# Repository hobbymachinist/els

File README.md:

# STM32 - Electronic Leadscrew

Electronic Leadscrew with STM32

## Demos

Some short demos available on YouTube

https://www.youtube.com/channel/UCVE05OvPm0yVd1yQSVZ0YSA/videos

## Building

```
git clone https://github.com/libopencm3/libopencm3
export OPENCM3_DIR=$PWD/libopencm3

cd libopencm3
make

cd ../
git clone <repo-url>
cd els

# edit Makefile to pick target and a TFT version
make TFT=ILI9481

# or
make TFT=ILI9486

# or
make TFT=ILI9488
```

Some ILITEK ICs use a non-standard 556 16-bit colorspace, use `COLORS=TFT_RGB_556` option in that case.

```
make TFT=ILI9488 COLORS=TFT_RGB_556
```

## Technical documentation

See [Technical Documentation](docs/els.md)

## Design ideas & Reference

- https://github.com/clough42/electronic-leadscrew
- https://github.com/prototypicall/Didge

## Goals / Features

1. The initial software is going to focus on being functional.
2. There is huge scope for optimisation, which can be something I might look into down the track.
3. Eventually, I'd like to add a G-code parser and motion controller to enable optional CNC control.

### Working with limited testing

* Z axis control for manual turning and threading operations
* Soft limits on Z & X
* Hard limits on Z & X
* Backlash compensation for leadscrews
* Semi automated cycles:
    - Turning
    - Threading
    - External Tapers
    - Internal Tapers
    - External Arcs
* Optional DRO support for:
    - TTL optical scales

### Wishlist / TO DO

* Semi automated cycles:
    - Internal Arc
    - External groove
    - Internal groove
* Tool radius compensation

## Pull Requests

Please reach out to discuss any major rewrites or changes if you wish to merge the changes upstream.

A lot of the firmware was developed over a few years on and off when I could find time to code and think about how I'd use it.
I don't want to disappoint or stop anyone from improving the software or hardware design but the primary focus of this work is
for my own personal use and don't want anything to distract me from that in a significant fashion. I don't have plenty of spare
time to review design changes or major software changes.

## IMPORTANT - PLEASE READ

Lathes are not toys, you can get injured or hurt someone else if you're not careful. Use this software at your
own risk.

This software is not provided with any warranty or support. It has only had limited testing in a home / hobby use setting
and may result in you getting injured or your equipment getting damaged due to errors in programming.

The author does not take any responsibility for the use of this software by others and cannot be held liable for any damages
that may result from its use.

## LICENSE

https://opensource.org/licenses/GPL-3.0

Free to be used in any fashion without royalty but any changes to hardware or software should be attributed and publicly shared
for the benefit of others.

Some of the code in this project uses snippets of code from [Adafruit GFX](https://github.com/adafruit/Adafruit-GFX-Library/)

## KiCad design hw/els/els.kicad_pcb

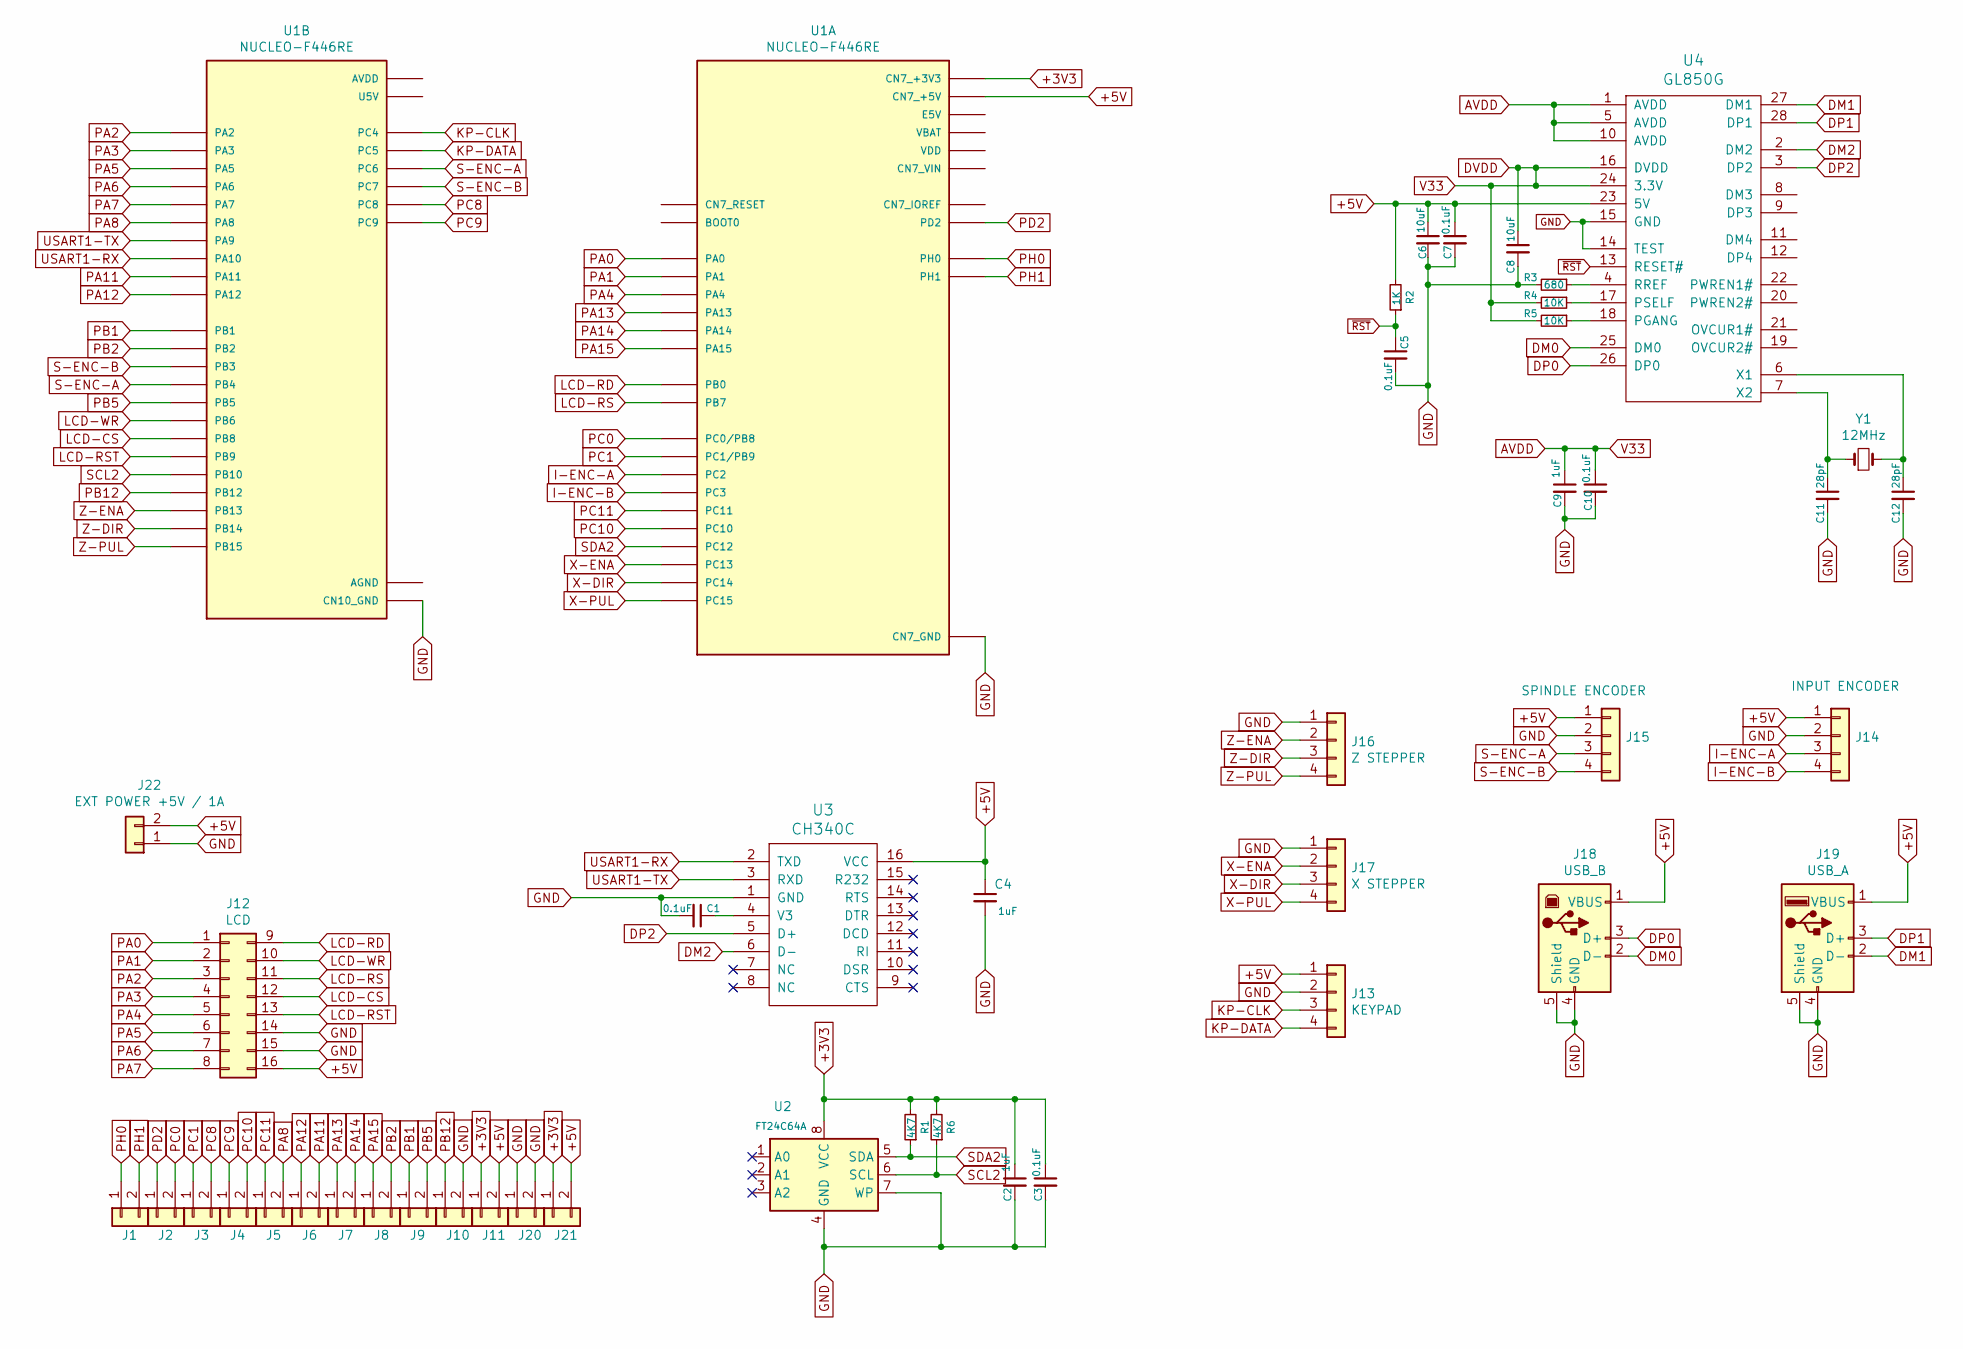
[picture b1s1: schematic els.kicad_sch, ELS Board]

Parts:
C1, C3, C5, C7, C10: 0.1uF; C_0805_2012Metric_Pad1.15x1.40mm_HandSolder
C2, C4, C9: 1uF; C_0805_2012Metric_Pad1.15x1.40mm_HandSolder
C6, C8: 10uF; C_0805_2012Metric_Pad1.15x1.40mm_HandSolder
C11, C12: 28pF; C_0805_2012Metric_Pad1.15x1.40mm_HandSolder
J1, J2, J3, J4, J5, J6, J7, J8, J9, J10, J11, J20, J21: Conn_01x02; TerminalBlock_bornier-2_P5.08mm
J12: LCD; IDC-Header_2x08_P2.54mm_Vertical
J13: KEYPAD; PinSocket_1x04_P2.54mm_Vertical
J14: INPUT ENCODER; PinSocket_1x04_P2.54mm_Vertical
J15: SPINDLE ENCODER; PinSocket_1x04_P2.54mm_Vertical
J16: Z STEPPER; PinSocket_1x04_P2.54mm_Vertical
J17: X STEPPER; PinSocket_1x04_P2.54mm_Vertical
J18: USB_B; USB_B_OST_USB-B1HSxx_Horizontal
J19: USB_A; USB_A_CONNFLY_DS1095-WNR0
J22: EXT POWER +5V / 1A; TerminalBlock_bornier-2_P5.08mm
R1, R6: 4K7; R_0805_2012Metric_Pad1.15x1.40mm_HandSolder
R2: 1K; R_0805_2012Metric_Pad1.15x1.40mm_HandSolder
R3: 680; R_0805_2012Metric_Pad1.15x1.40mm_HandSolder
R4, R5: 10K; R_0805_2012Metric_Pad1.15x1.40mm_HandSolder
U1: NUCLEO-F446RE; MODULE_NUCLEO-F446RE; PARTREV 13
U2: FT24C64A; SO-8_5.3x6.2mm_P1.27mm
U3: CH340C; SOIC-16_3.9x9.9mm_P1.27mm
U4: GL850G; SSOP-28_5.3x10.2mm_P0.65mm
Y1: 12MHz; Crystal_HC49-4H_Vertical

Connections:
+3V3: C2.1, C3.1, J11.1, J21.1, R1.2, R6.2, U1.CN7_16 (CN7_+3V3), U2.8 (VCC)
+5V: C4.1, C6.1, C7.1, J11.2, J12.16, J13.1, J14.1, J15.1, J18.1 (VBUS), J19.1 (VBUS), J21.2, J22.2, R2.2, U1.CN7_18 (CN7_+5V), U3.16 (VCC), U4.23 (5V)
AVDD: C8.1, C9.1, C10.1, R4.2, R5.2, U4.1 (AVDD), U4.5 (AVDD), U4.10 (AVDD), U4.16 (DVDD), U4.24 (3.3V)
DM0: J18.2 (D-), U4.25 (DM0)
DM1: J19.2 (D-), U4.27 (DM1)
DM2: U3.6 (D-), U4.2 (DM2)
DP0: J18.3 (D+), U4.26 (DP0)
DP1: J19.3 (D+), U4.28 (DP1)
DP2: U3.5 (D+), U4.3 (DP2)
GND: C1.2, C2.2, C3.2, C4.2, C5.2, C6.2, C7.2, C8.2, C9.2, C10.2, C11.2, C12.2, J10.2, J12.14, J12.15, J13.2, J14.2, J15.2, J16.1, J17.1, J18.4 (GND), J18.5 (Shield), J19.4 (GND), J19.5 (Shield), J20.1, J20.2, J22.1, R3.2, U1.CN7_8 (CN7_GND), U1.CN7_19 (CN7_GND), U1.CN7_20 (CN7_GND), U1.CN7_22 (CN7_GND), U1.CN10_9 (CN10_GND), U1.CN10_20 (CN10_GND), U2.4 (GND), U2.7 (WP), U3.1 (GND), U4.14 (TEST), U4.15 (GND); also elsewhere on the board
I-ENC-A: J14.3, U1.CN7_35 (PC2)
I-ENC-B: J14.4, U1.CN7_37 (PC3)
KP-CLK: J13.3, U1.CN10_34 (PC4)
KP-DATA: J13.4, U1.CN10_6 (PC5)
LCD-CS: J12.12, U1.CN10_3 (PB8)
LCD-RD: J12.9, U1.CN7_34 (PB0)
LCD-RS: J12.11, U1.CN7_21 (PB7)
LCD-RST: J12.13, U1.CN10_5 (PB9)
LCD-WR: J12.10, U1.CN10_17 (PB6)
unnamed: C1.1, U3.4 (V3)
unnamed: C11.1, U4.7 (X2), Y1.1
unnamed: C12.1, U4.6 (X1), Y1.2
unnamed: R3.1, U4.4 (RREF)
unnamed: R4.1, U4.17 (PSELF)
unnamed: R5.1, U4.18 (PGANG)
PA0: J12.1, U1.CN7_28 (PA0)
PA1: J12.2, U1.CN7_30 (PA1)
PA2: J12.3, U1.CN10_35 (PA2)
PA3: J12.4, U1.CN10_37 (PA3)
PA4: J12.5, U1.CN7_32 (PA4)
PA5: J12.6, U1.CN10_11 (PA5)
PA6: J12.7, U1.CN10_13 (PA6)
PA7: J12.8, U1.CN10_15 (PA7)
PA8: J5.2, U1.CN10_23 (PA8)
PA11: J6.2, U1.CN10_14 (PA11)
PA12: J6.1, U1.CN10_12 (PA12)
PA13: J7.1, U1.CN7_13 (PA13)
PA14: J7.2, U1.CN7_15 (PA14)
PA15: J8.1, U1.CN7_17 (PA15)
PB1: J9.1, U1.CN10_24 (PB1)
PB2: J8.2, U1.CN10_22 (PB2)
PB5: J9.2, U1.CN10_29 (PB5)
PB12: J10.1, U1.CN10_16 (PB12)
PC0: J2.2, U1.CN7_38 (PC0/PB8)
PC1: J3.1, U1.CN7_36 (PC1/PB9)
PC8: J3.2, U1.CN10_2 (PC8)
PC9: J4.1, U1.CN10_1 (PC9)
PC10: J4.2, U1.CN7_1 (PC10)
PC11: J5.1, U1.CN7_2 (PC11)
PD2: J2.1, U1.CN7_4 (PD2)
PH0: J1.1, U1.CN7_29 (PH0)
PH1: J1.2, U1.CN7_31 (PH1)
S-ENC-A: J15.3, U1.CN10_4 (PC6), U1.CN10_27 (PB4)
S-ENC-B: J15.4, U1.CN10_19 (PC7), U1.CN10_31 (PB3)
SCL2: R6.1, U1.CN10_25 (PB10), U2.6 (SCL)
SDA2: R1.1, U1.CN7_3 (PC12), U2.5 (SDA)
USART1-RX: U1.CN10_33 (PA10), U3.2 (TXD)
USART1-TX: U1.CN10_21 (PA9), U3.3 (RXD)
X-DIR: J17.3, U1.CN7_25 (PC14)
X-ENA: J17.2, U1.CN7_23 (PC13)
X-PUL: J17.4, U1.CN7_27 (PC15)
Z-DIR: J16.3, U1.CN10_28 (PB14)
Z-ENA: J16.2, U1.CN10_30 (PB13)
Z-PUL: J16.4, U1.CN10_26 (PB15)
~RST: C5.1, R2.1, U4.13 (RESET#)

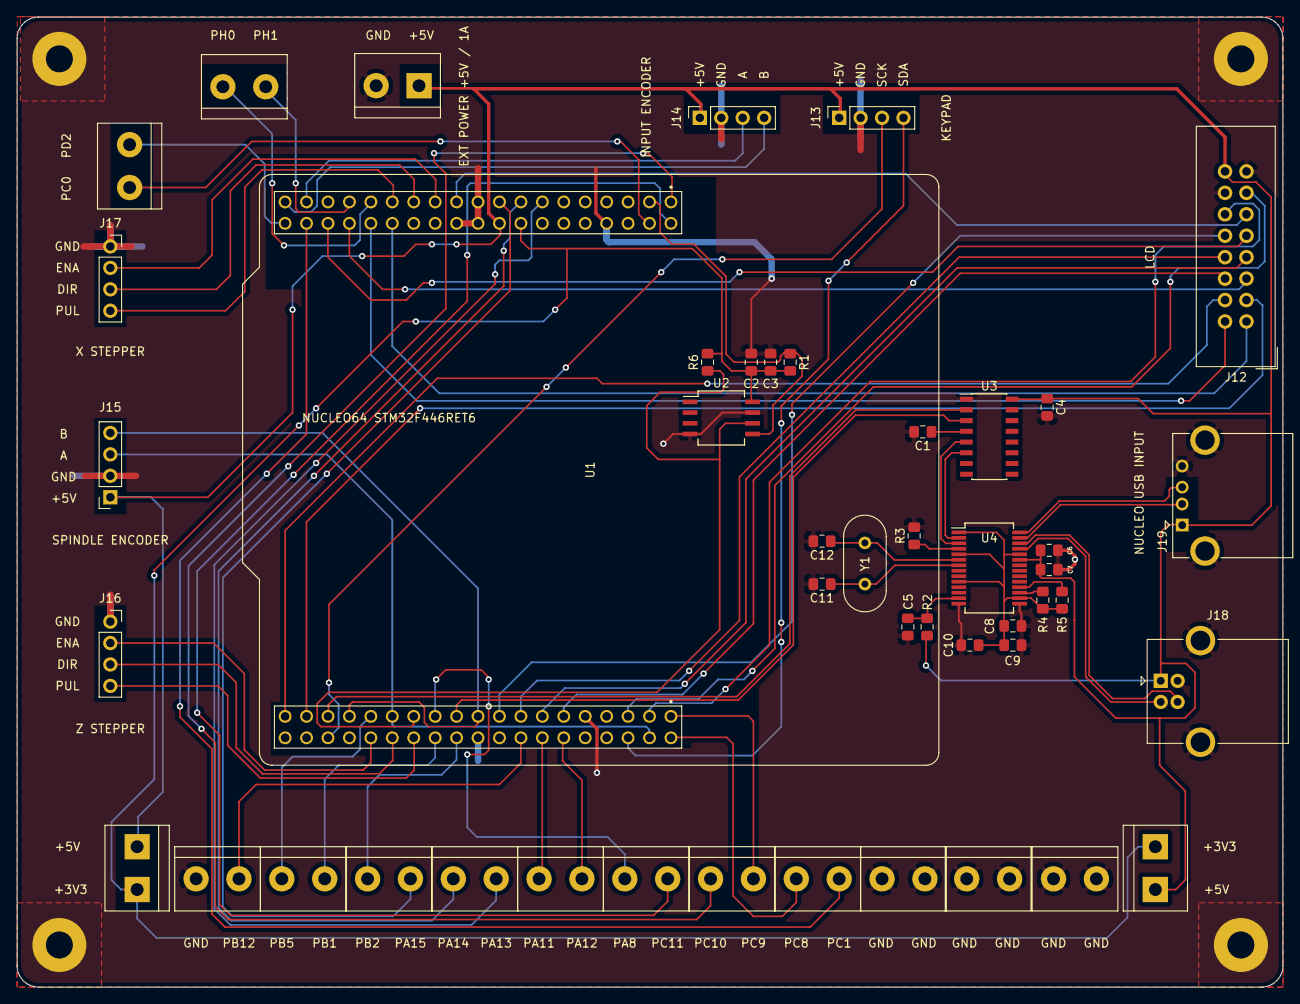
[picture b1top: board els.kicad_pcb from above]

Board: 2 copper layers, 150.0 x 114.9 mm, 47 parts (0 on the bottom side), 65 nets.

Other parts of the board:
J20#2, J20#3: Conn_01x02; TerminalBlock_bornier-2_P5.08mm

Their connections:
GND: J20#2.1, J20#2.2, J20#3.1, J20#3.2; also elsewhere on the board

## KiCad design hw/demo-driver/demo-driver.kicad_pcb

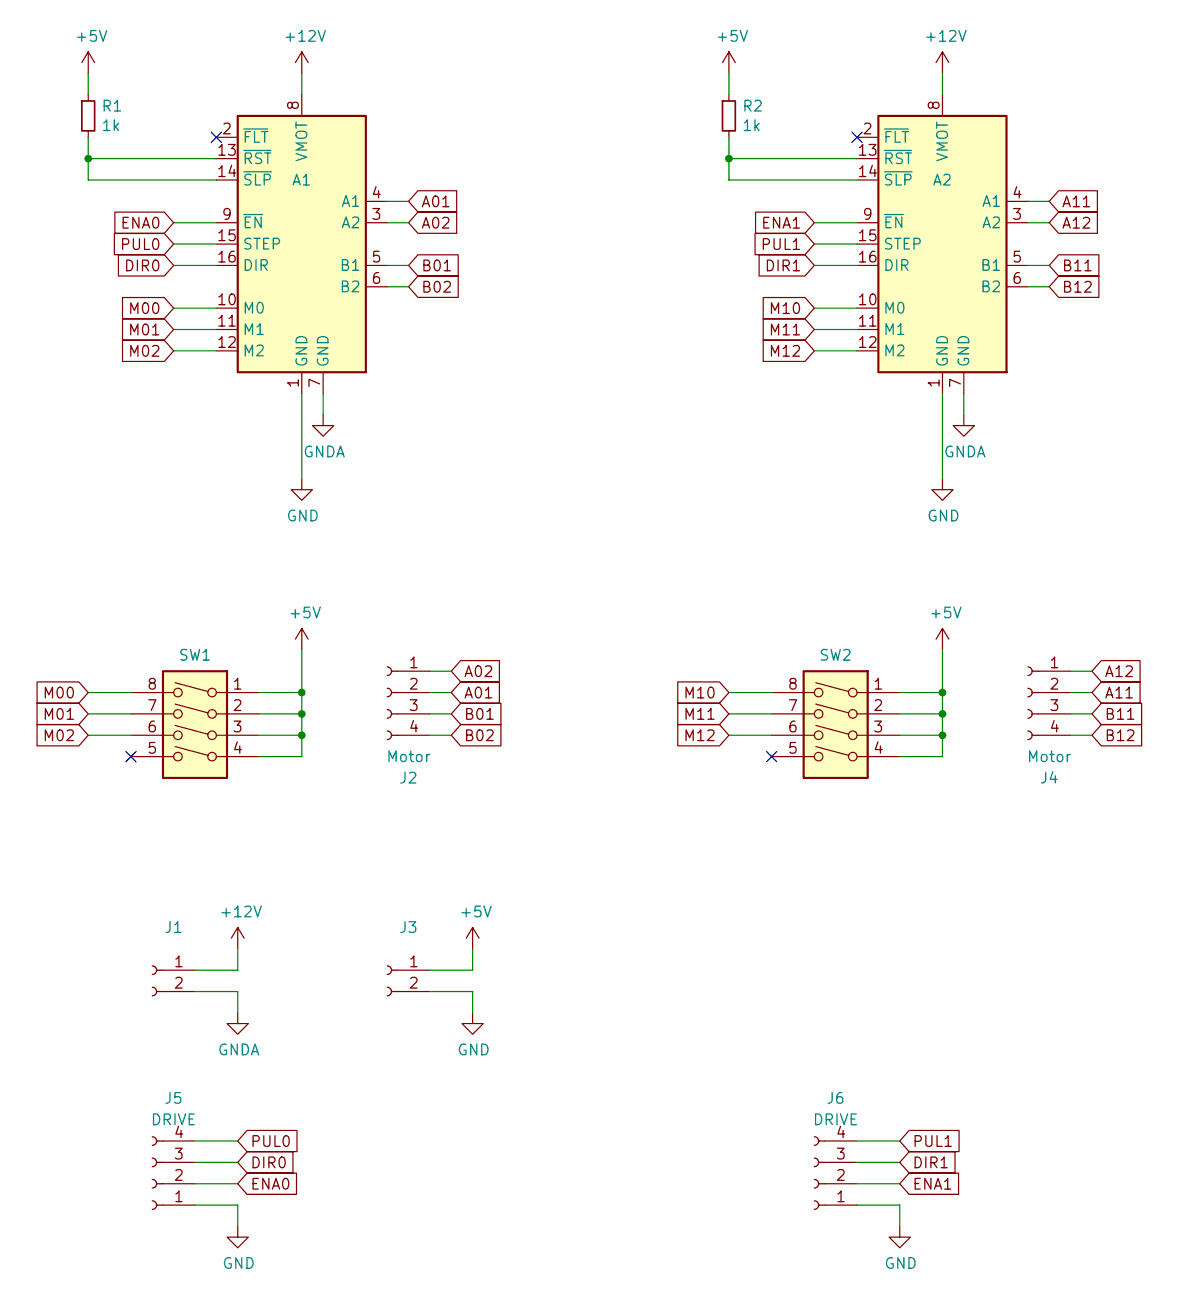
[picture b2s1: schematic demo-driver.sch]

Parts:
A1, A2: Pololu_Breakout_DRV8825; Pololu_Breakout-16_15.2x20.3mm
J1: VMOTOR; TerminalBlock_bornier-2_P5.08mm
J2, J4: Motor; PinSocket_1x04_P2.54mm_Horizontal
J3: VLOGIC; TerminalBlock_bornier-2_P5.08mm
J5, J6: DRIVE; PinSocket_1x04_P2.54mm_Horizontal
R1, R2: 1k; R_0805_2012Metric_Pad1.15x1.40mm_HandSolder
SW1, SW2: MICROSTEP; SW_DIP_SPSTx04_Slide_9.78x12.34mm_W7.62mm_P2.54mm

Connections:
+5V: J3.1, R1.1, R2.1, SW1.1, SW1.2, SW1.3, SW1.4, SW2.1, SW2.2, SW2.3, SW2.4
+12V: A1.8 (VMOT), A2.8 (VMOT), J1.1
A01: A1.4 (A1), J2.2
A02: A1.3 (A2), J2.1
A11: A2.4 (A1), J4.2
A12: A2.3 (A2), J4.1
B01: A1.5 (B1), J2.3
B02: A1.6 (B2), J2.4
B11: A2.5 (B1), J4.3
B12: A2.6 (B2), J4.4
DIR0: A1.16 (DIR), J5.3
DIR1: A2.16 (DIR), J6.3
ENA0: A1.9 (~EN), J5.2
ENA1: A2.9 (~EN), J6.2
GND: A1.1 (GND), A2.1 (GND), J3.2, J5.1, J6.1
GNDA: A1.7 (GND), A2.7 (GND), J1.2
M00: A1.10 (M0), SW1.8
M01: A1.11 (M1), SW1.7
M02: A1.12 (M2), SW1.6
M10: A2.10 (M0), SW2.8
M11: A2.11 (M1), SW2.7
M12: A2.12 (M2), SW2.6
unnamed: A1.13 (~RST), A1.14 (~SLP), R1.2
unnamed: A2.13 (~RST), A2.14 (~SLP), R2.2
PUL0: A1.15 (STEP), J5.4
PUL1: A2.15 (STEP), J6.4

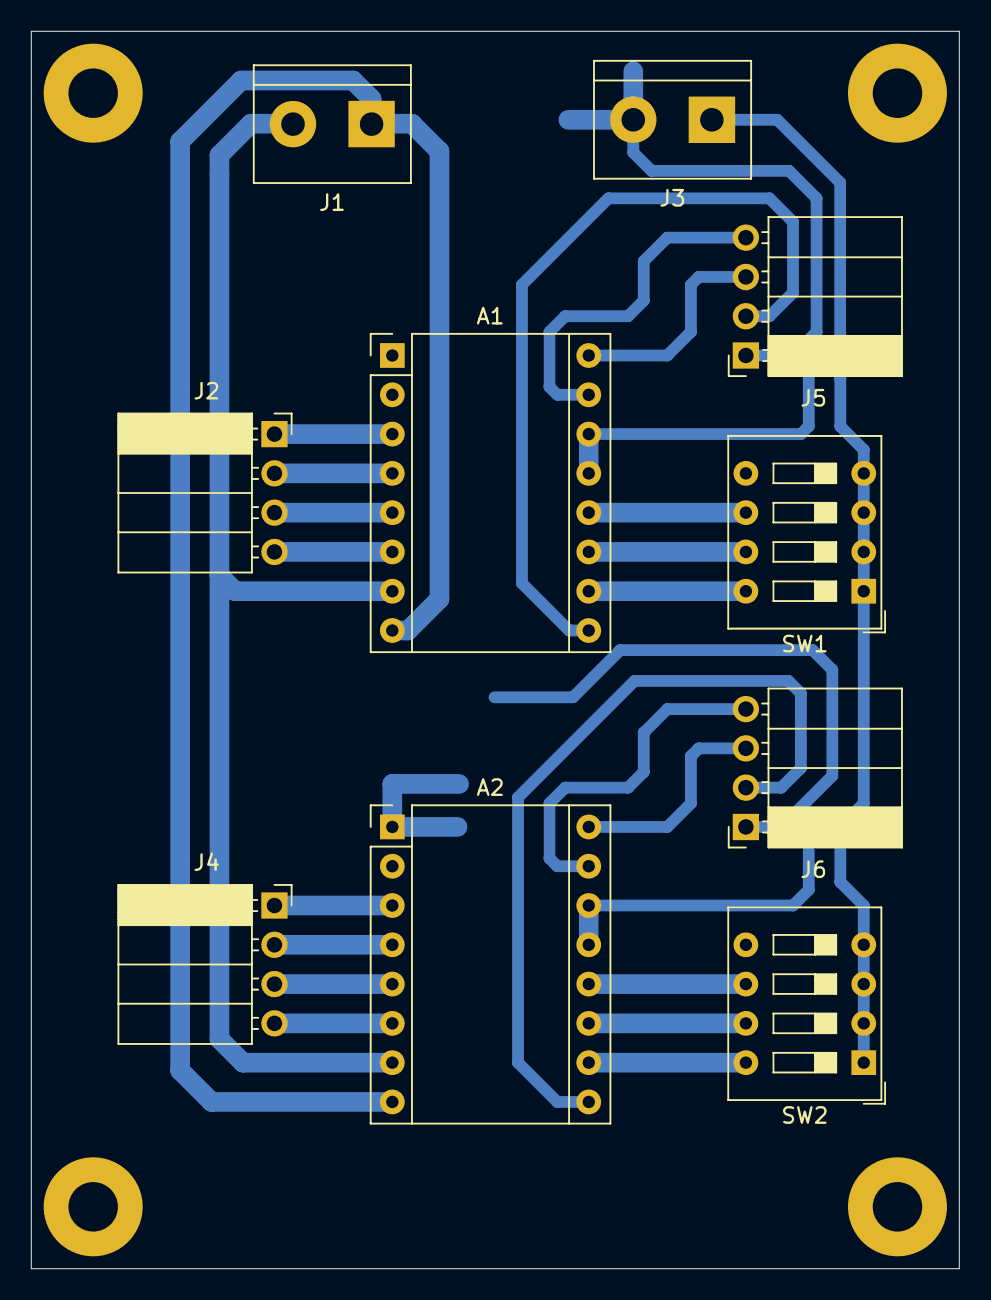
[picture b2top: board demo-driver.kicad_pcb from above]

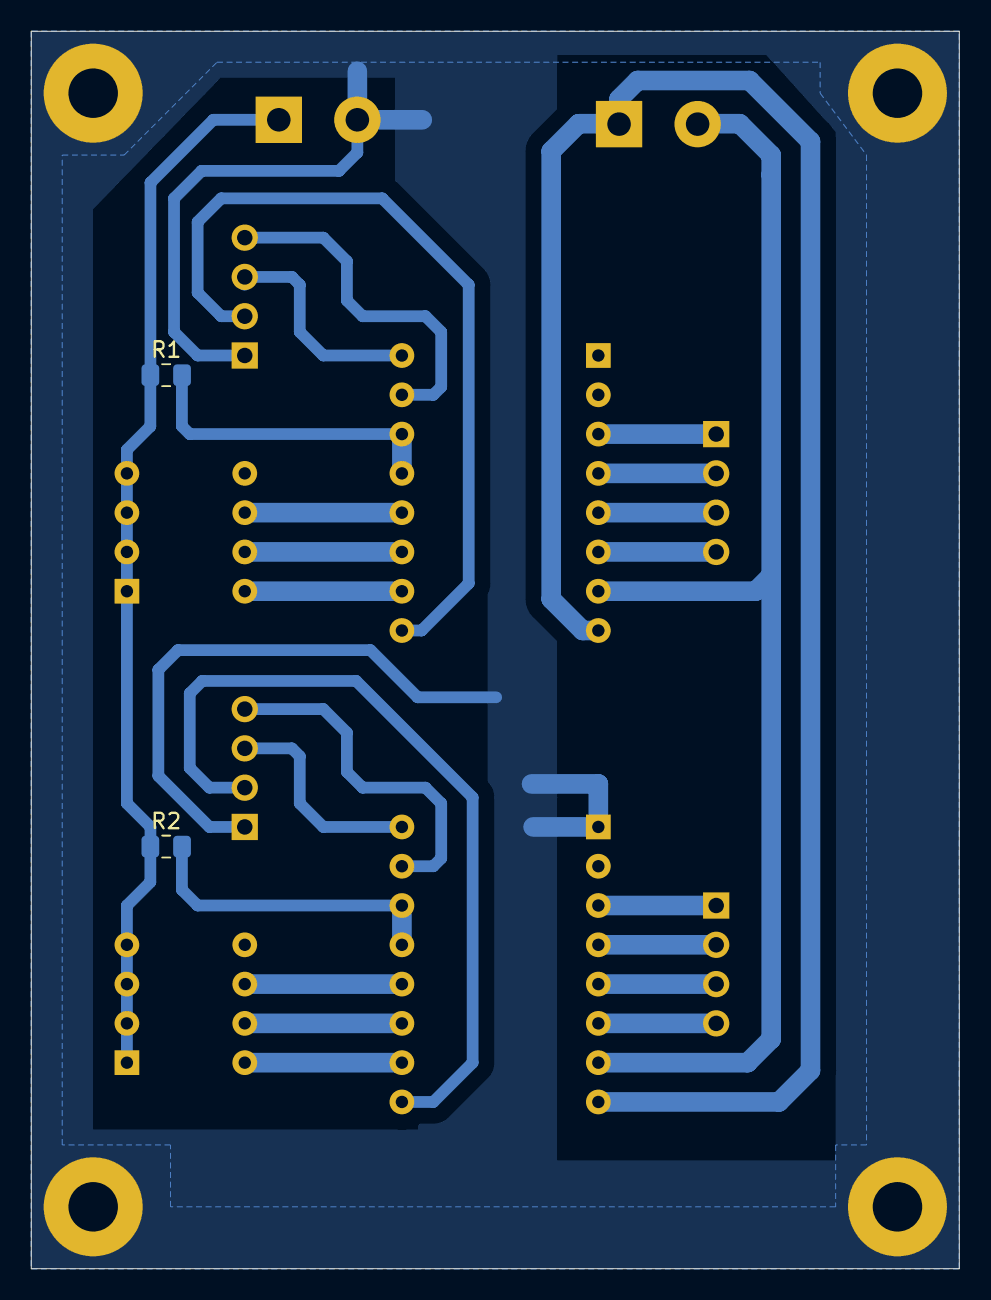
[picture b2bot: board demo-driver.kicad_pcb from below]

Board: 2 copper layers, 60.0 x 80.0 mm, 12 parts (2 on the bottom side), 26 nets.

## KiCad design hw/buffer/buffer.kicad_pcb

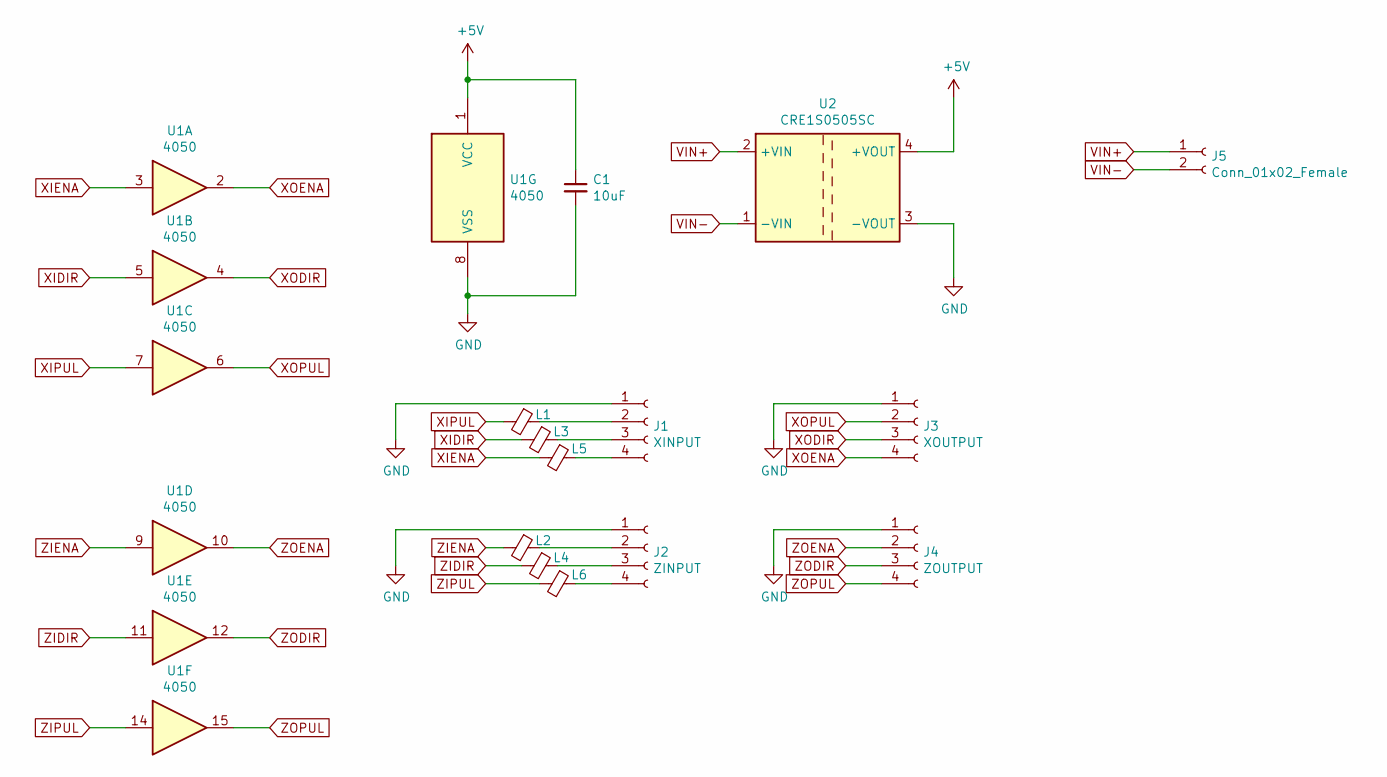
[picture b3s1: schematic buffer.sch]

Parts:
C1: 10uF; C_0805_2012Metric_Pad1.15x1.40mm_HandSolder
J1: XINPUT; TerminalBlock_bornier-4_P5.08mm
J2: ZINPUT; TerminalBlock_bornier-4_P5.08mm
J3: XOUTPUT; TerminalBlock_bornier-4_P5.08mm
J4: ZOUTPUT; TerminalBlock_bornier-4_P5.08mm
J5: Conn_01x02_Female; TerminalBlock_bornier-2_P5.08mm
L1, L2, L3, L4, L5, L6: Ferrite_Bead_Small; L_0805_2012Metric_Pad1.15x1.40mm_HandSolder
U1: 4050; DIP-16_W7.62mm_Socket_LongPads
U2: CRE1S0505SC; Converter_DCDC_muRata_CRE1xxxxxxSC_THT

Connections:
+5V: C1.1, U1.1 (VCC), U2.4 (+VOUT)
GND: C1.2, J1.1, J2.1, J3.1, J4.1, U1.8 (VSS), U2.3 (-VOUT)
unnamed: J1.2, L1.1
unnamed: J1.3, L3.1
unnamed: J1.4, L5.1
unnamed: J2.2, L2.1
unnamed: J2.3, L4.1
unnamed: J2.4, L6.1
VIN+: J5.1, U2.2 (+VIN)
VIN-: J5.2, U2.1 (-VIN)
XIDIR: L3.2, U1.5
XIENA: L5.2, U1.3
XIPUL: L1.2, U1.7
XODIR: J3.3, U1.4
XOENA: J3.4, U1.2
XOPUL: J3.2, U1.6
ZIDIR: L4.2, U1.11
ZIENA: L2.2, U1.9
ZIPUL: L6.2, U1.14
ZODIR: J4.3, U1.12
ZOENA: J4.2, U1.10
ZOPUL: J4.4, U1.15

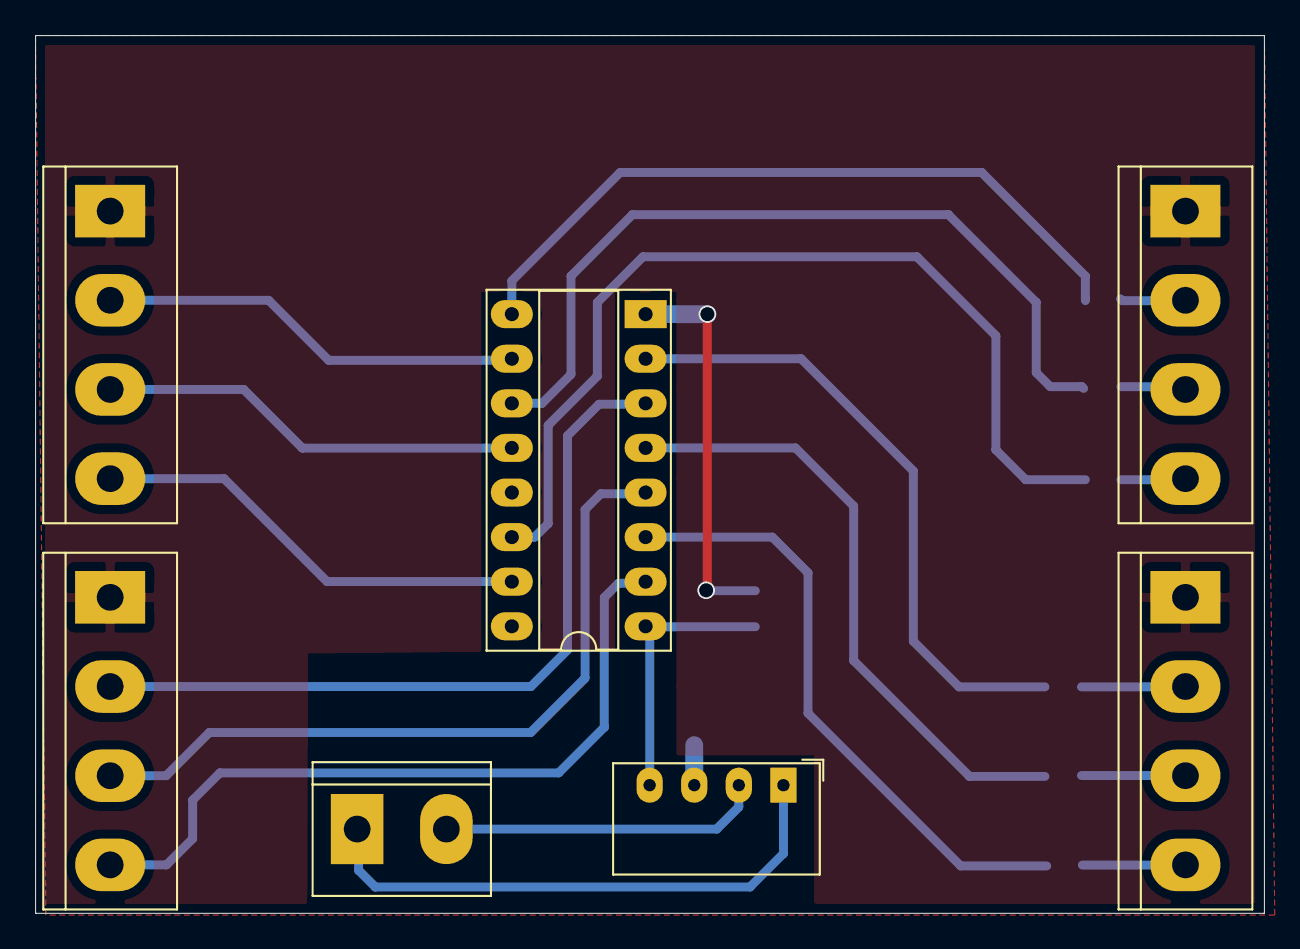
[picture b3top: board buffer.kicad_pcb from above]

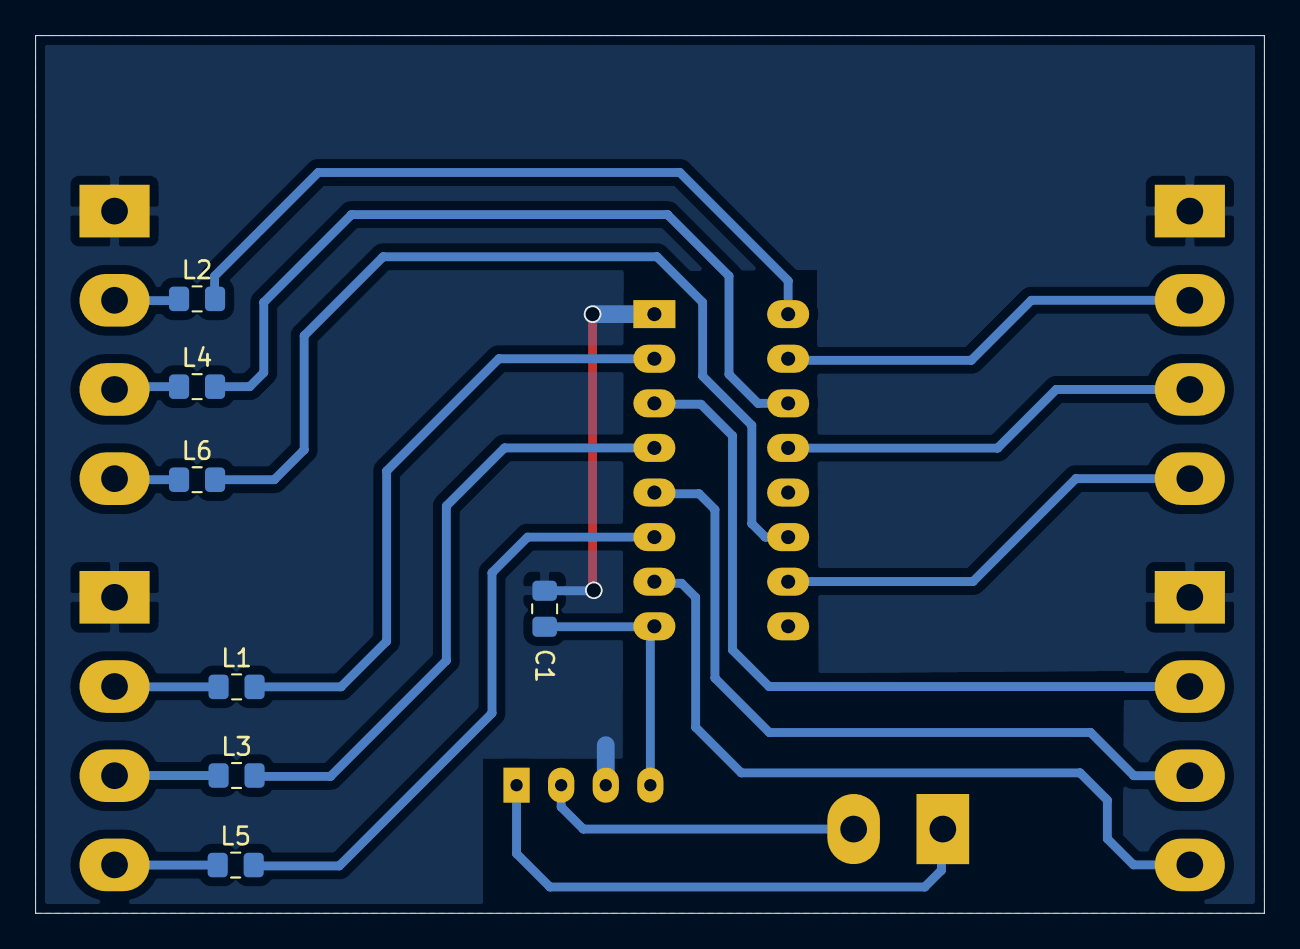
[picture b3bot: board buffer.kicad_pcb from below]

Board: 2 copper layers, 70.0 x 50.0 mm, 14 parts (7 on the bottom side), 22 nets.

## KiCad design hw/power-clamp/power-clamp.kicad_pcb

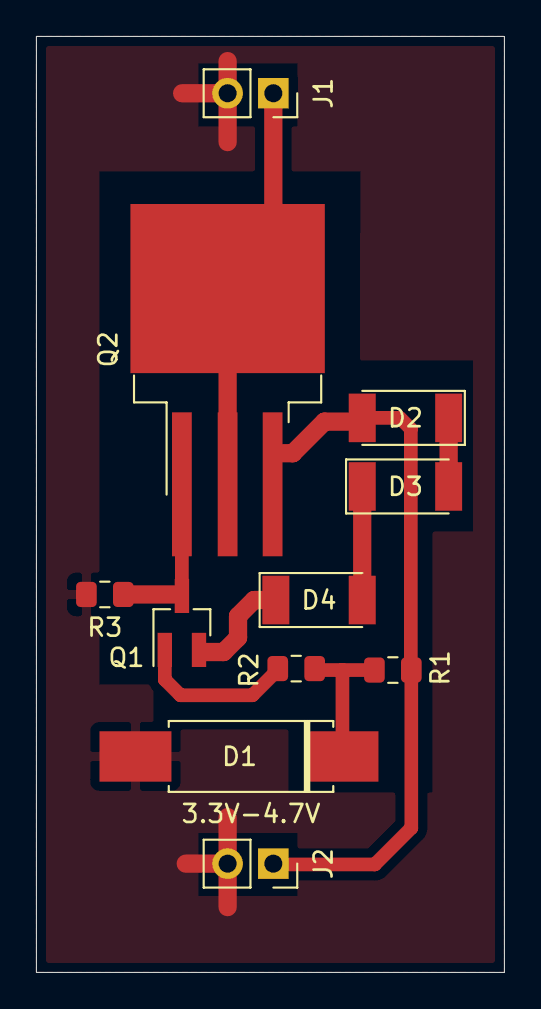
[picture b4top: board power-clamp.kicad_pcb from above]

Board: 2 copper layers, 26.0 x 52.0 mm, 11 parts (0 on the bottom side), 9 nets.

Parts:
D1: 3.3V or 4.7V; D_5W_P10.16mm_Horizontal
D2, D3, D4: D_Small_ALT; D_MELF
J1: OUT; PinSocket_1x02_P2.54mm_Vertical
J2: IN; PinSocket_1x02_P2.54mm_Vertical
Q1: Q_PNP_BEC; SOT-23_Handsoldering
Q2: Q_PMOS_GDS; TO-263-3_TabPin2
R1: 1K; R_0805_2012Metric_Pad1.15x1.40mm_HandSolder
R2, R3: 10K; R_0805_2012Metric_Pad1.15x1.40mm_HandSolder

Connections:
+5V: J1.1, Q2.2
GNDA: D1.2, J1.2, J2.2, R3.2
unnamed: D1.1, R1.2, R2.2
unnamed: D2.1, D3.2
unnamed: D3.1, D4.2
unnamed: D4.1, Q1.2
unnamed: Q1.1, R2.1
unnamed: Q1.3, Q2.1, R3.1
VCC: D2.2, J2.1, Q2.3, R1.1

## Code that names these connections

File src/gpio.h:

#pragma once

#include <errno.h>
#include <math.h>
#include <stdio.h>
#include <stdlib.h>
#include <libopencm3/cm3/dwt.h>
#include <libopencm3/cm3/nvic.h>
#include <libopencm3/stm32/rcc.h>
#include <libopencm3/stm32/flash.h>
#include <libopencm3/stm32/spi.h>
#include <libopencm3/stm32/gpio.h>
#include <libopencm3/stm32/usart.h>
#include <libopencm3/stm32/exti.h>

#ifdef __cplusplus
extern "C" {
#endif

typedef struct {
  uint32_t port;
  uint32_t pin;
} els_gpio_t;

//==============================================================================
// GPIO Mapping Summary.
//==============================================================================

// PA0  - TFT Data
// PA1  - TFT Data
// PA2  - TFT Data
// PA3  - TFT Data
// PA4  - TFT Data
// PA5  - TFT Data
// PA6  - TFT Data
// PA7  - TFT Data
// PA8  - RESERVED
// PA9  - USART TX
// PA10 - USART RX
// PA11 - DRO X-A (Int)
// PA12 - DRO X-B (Int)
// PA13 - RESERVED
// PA14 - RESERVED
// PA15 - RESERVED
//
// PB0  - TFT RD
// PB1  - DRO Z-A (Int)
// PB2  - RESERVED
// PB3  - Spindle Enc A (Int)
// PB4  - Spindle Enc B
// PB5  - DRO Z-B (Int)
// PB6  - TFT WR
// PB7  - TFT RS
// PB8  - TFT CS
// PB9  - TFT RST
// PB10 - EEPROM SCL
// PB11 - N/A
// PB12 - RESERVED
// PB13 - Z ENA
// PB14 - Z DIR
// PB15 - Z PUL
//
// PC0  -
// PC1  -
// PC2  - Input Enc A (Int)
// PC3  - Input Enc B
// PC4  - PS/2 Keypad CLK (Int)
// PC5  - PS/2 Keypad DAT
// PC6  - Spindle Enc A (Timer)
// PC7  - Spindle Enc B (Timer)
// PC8  - RESERVED
// PC9  - RESERVED
// PC10 -
// PC11 -
// PC12 - EEPROM SDA
// PC13 - X ENA
// PC14 - X DIR
// PC15 - X PUL
//
// PH0  -
// PH1  -
//==============================================================================

void els_gpio_setup(void);
void els_gpio_mode_input(uint32_t port, uint32_t pins);
void els_gpio_mode_output(uint32_t port, uint32_t pins);

//==============================================================================
// Helpers
//==============================================================================

#define els_gpio_get(port, pins)   (GPIO_IDR(port) & pins)
#define els_gpio_set(port, pins)   GPIO_BSRR(port) = pins
#define els_gpio_clear(port, pins) GPIO_BSRR(port) = (pins << 16)
#define els_gpio_toggle(port, pins) do { \
                                      uint32_t data   = GPIO_ODR(port); \
                                      GPIO_BSRR(port) = ((data & pins) << 16) | (~data & pins); \
                                    } while(0)

#ifdef __cplusplus
}
#endif

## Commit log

2022-01-16 initial commit.
2022-01-18 update docs.
2022-01-28 updated docs & hw notes.
2022-01-28 update docs, optional usart input.
2022-01-28 update docs, dro input.
2022-04-09 new turning operations & prelim closed loop support.
2022-04-16 add cut diamond knurling.
2022-06-06 platform tft changed
    the origional files contaones a link to the files in platform/
2022-06-06 changed keyboard mapping
2022-10-12 various bugfixes and improvements.
2022-10-13 simplify stepper acceleration logic.
2022-10-13 Initial migration of els Kicad files to Kicad 6.0
2022-10-13 update kicad 3d model paths.
2022-10-13 simplify tft platform definitions.
2022-10-17 minor cleanup / optimisations.
2022-10-26 increase thread pitch resolution & bug fixes.
2022-11-01 simplify trapezoidal velocity profile for jogging.
    simplify trapezoidal velocity profile
    add config option for jog velocity
2023-02-15 some new features, new functions & bugfixes
    added parting, facing
    added roughing & finishing pass config for turning.
2023-03-18 updated docs & ext threading improvements.
2023-03-24 feature improvements & updates
    - streamline manual turning & threading jog functions
    - simplify keypad functions
    - replaced min/max jog min/jog max with jog to origin
    - add jog to origin across all modules
    - add closed loop support for manual turning and threading
2023-03-24 add missing turning screenshot.
2023-04-15 Update hand wheel encoder hw description
    There are a few different options for the hand wheel encoder. According to the schematic, this was built with the 4-wire 5v version in mind.
2023-05-21 Update els.md
    Add solder bridge modifications & changes.
2023-05-31 refactoring & improvements.
2023-06-01 refactoring to support multiple tft controller ICs.
    at this time only supporting ilitek family with 8-bit parallel data bus.
2023-06-01 fine tune twrl for write strobing.
2023-06-02 cleanup Makefile.
2023-06-02 ILI9488 color correction.
2023-06-03 fix ili9488 driver init.
2023-06-03 timing tweaks for ILI9488.
2023-06-03 update ili9481 vcom & power init.
    vcom amplitude should be < 6v
